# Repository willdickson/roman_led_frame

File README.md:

# Roman LED Frame 
Ancient Roman Rectangular LED frame. For puzzlebox experiments. 

* [Bill-of-materials](BOM.txt)

# 3D View

# License: 
Creative Commons Attribution 4.0 International CC BY 4.0

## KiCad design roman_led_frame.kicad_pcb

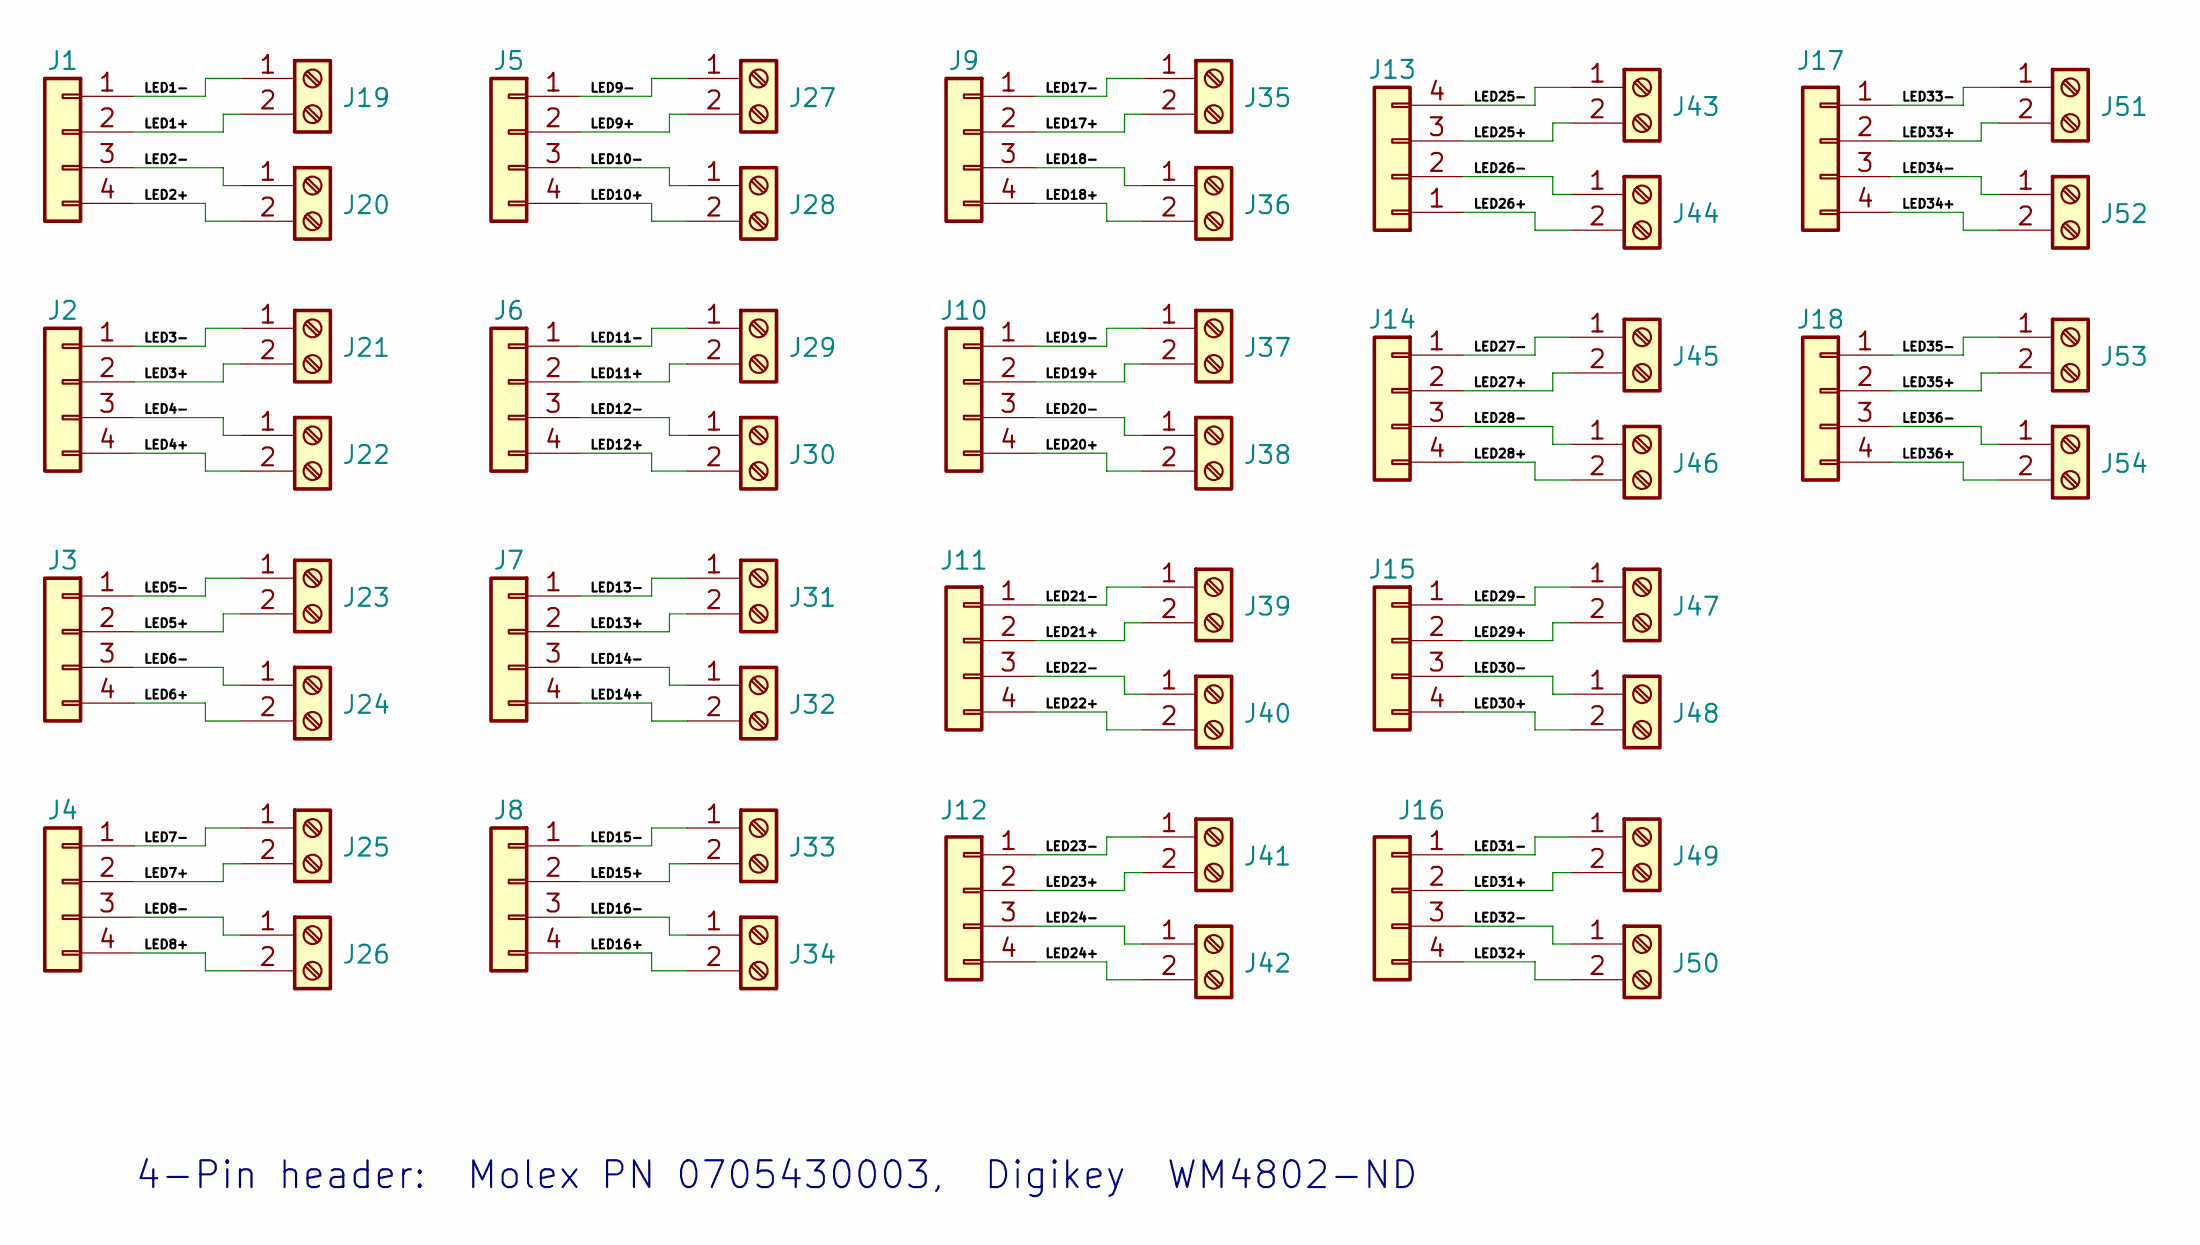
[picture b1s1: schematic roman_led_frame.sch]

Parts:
J1, J2, J3, J4, J5, J6, J7, J8, J9, J10, J11, J12, J13, J14, J15, J16, J17, J18: Conn_01x04; 0705430003
J19, J20, J21, J22, J23, J24, J25, J26, J27, J28, J29, J30, J31, J32, J33, J34, J35, J36, J37, J38, J39, J40, J41, J42, J43, J44, J45, J46, J47, J48, J49, J50, J51, J52, J53, J54: Screw_Terminal_01x02; BLOCK_CONN_2X1

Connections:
/LED1+: J1.2, J19.2
/LED1-: J1.1, J19.1
/LED2+: J1.4, J20.2
/LED2-: J1.3, J20.1
/LED3+: J2.2, J21.2
/LED3-: J2.1, J21.1
/LED4+: J2.4, J22.2
/LED4-: J2.3, J22.1
/LED5+: J3.2, J23.2
/LED5-: J3.1, J23.1
/LED6+: J3.4, J24.2
/LED6-: J3.3, J24.1
/LED7+: J4.2, J25.2
/LED7-: J4.1, J25.1
/LED8+: J4.4, J26.2
/LED8-: J4.3, J26.1
/LED9+: J5.2, J27.2
/LED9-: J5.1, J27.1
/LED10+: J5.4, J28.2
/LED10-: J5.3, J28.1
/LED11+: J6.2, J29.2
/LED11-: J6.1, J29.1
/LED12+: J6.4, J30.2
/LED12-: J6.3, J30.1
/LED13+: J7.2, J31.2
/LED13-: J7.1, J31.1
/LED14+: J7.4, J32.2
/LED14-: J7.3, J32.1
/LED15+: J8.2, J33.2
/LED15-: J8.1, J33.1
/LED16+: J8.4, J34.2
/LED16-: J8.3, J34.1
/LED17+: J9.2, J35.2
/LED17-: J9.1, J35.1
/LED18+: J9.4, J36.2
/LED18-: J9.3, J36.1
/LED19+: J10.2, J37.2
/LED19-: J10.1, J37.1
/LED20+: J10.4, J38.2
/LED20-: J10.3, J38.1
/LED21+: J11.2, J39.2
/LED21-: J11.1, J39.1
/LED22+: J11.4, J40.2
/LED22-: J11.3, J40.1
/LED23+: J12.2, J41.2
/LED23-: J12.1, J41.1
/LED24+: J12.4, J42.2
/LED24-: J12.3, J42.1
/LED25+: J13.3, J43.2
/LED25-: J13.4, J43.1
/LED26+: J13.1, J44.2
/LED26-: J13.2, J44.1
/LED27+: J14.2, J45.2
/LED27-: J14.1, J45.1
/LED28+: J14.4, J46.2
/LED28-: J14.3, J46.1
/LED29+: J15.2, J47.2
/LED29-: J15.1, J47.1
/LED30+: J15.4, J48.2
/LED30-: J15.3, J48.1
/LED31+: J16.2, J49.2
/LED31-: J16.1, J49.1
/LED32+: J16.4, J50.2
/LED32-: J16.3, J50.1
/LED33+: J17.2, J51.2
/LED33-: J17.1, J51.1
/LED34+: J17.4, J52.2
/LED34-: J17.3, J52.1
/LED35+: J18.2, J53.2
/LED35-: J18.1, J53.1
/LED36+: J18.4, J54.2
/LED36-: J18.3, J54.1

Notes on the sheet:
4-Pin header: Molex PN 0705430003, Digikey WM4802-ND

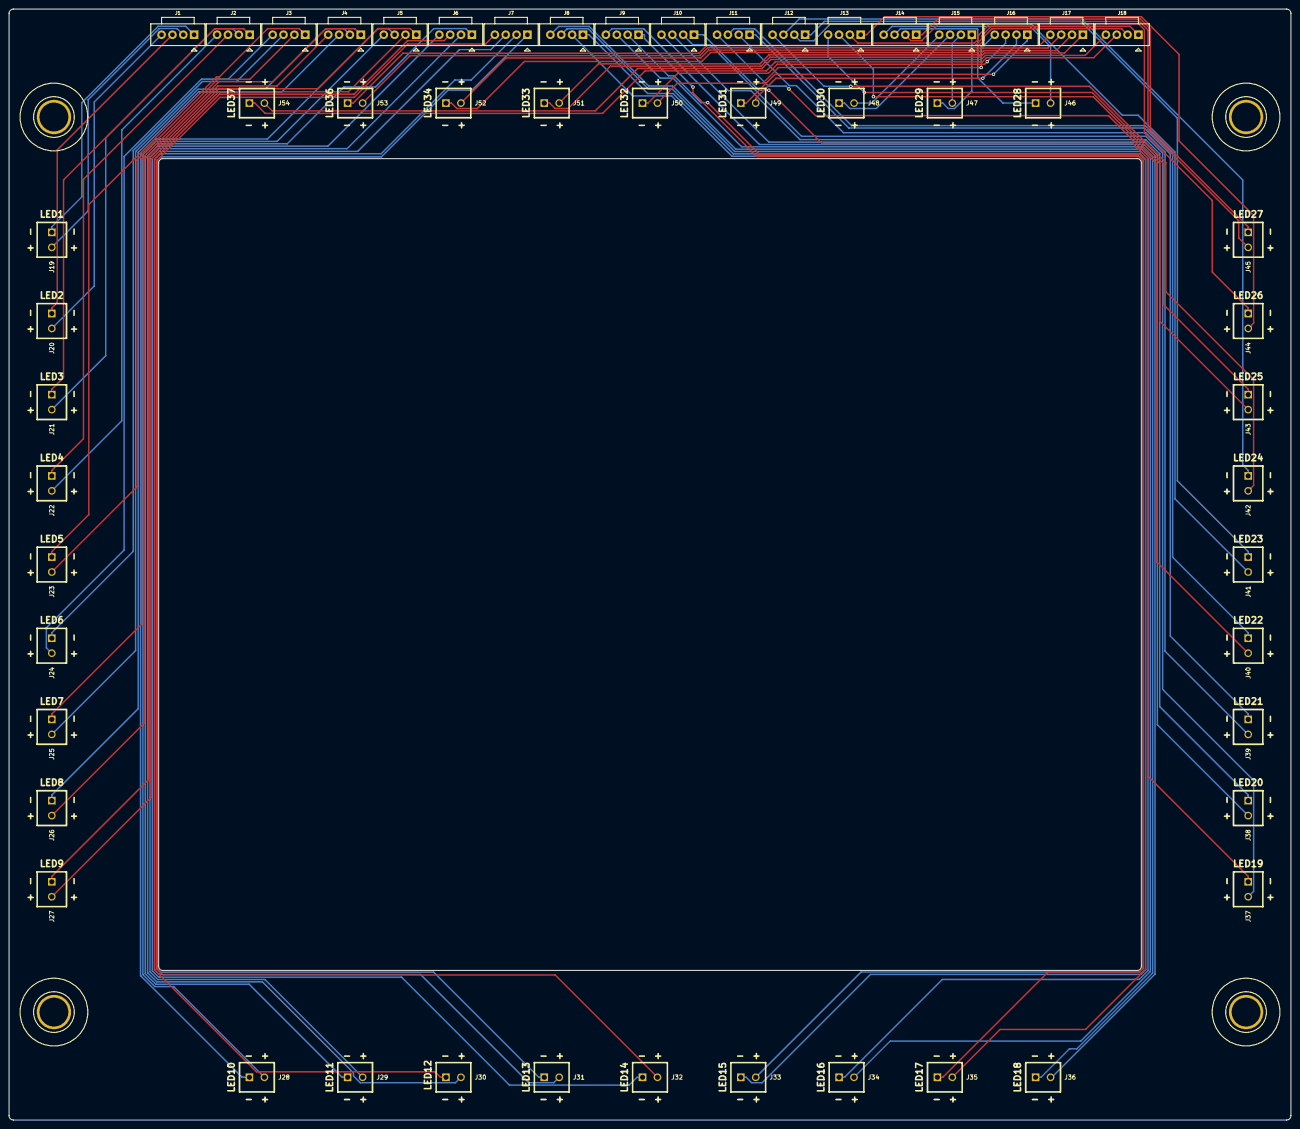
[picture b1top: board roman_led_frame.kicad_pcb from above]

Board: 2 copper layers, 300.0 x 260.0 mm, 58 parts (0 on the bottom side), 72 nets.

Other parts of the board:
M1, M2, M3, M4: quarter_twenty

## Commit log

2019-10-28 Project creation.
2019-10-30 Added gerber files for version v0.1.
